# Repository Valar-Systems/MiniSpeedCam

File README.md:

# MiniSpeedCam

## Intro
The MiniSpeedCam tracks vehicle speeds, takes a photo, and uploads the photo and speed data to a server. Use it to track vehicle speeds on your driveway or street.

**Please sign up to the waitlist at [minispeedcam.com](https://minispeedcam.com/) if you're interested in purchasing one. We have not began manufacturing these yet.**

<div style="text-align: center;">

</div>

The firmware is designed to work with [minispeedcam.com](https://minispeedcam.com/) and requires **absolutely no coding or flashing.** The device works right out of the box.

The device creates a WiFi access point when started for the first time. Connect to it with your phone or laptop and enter your WiFi credentials. It will automatically connect to the internet.

All photos and speed data is sent to your account on [minispeedcam.com](https://minispeedcam.com/) where the data can be viewed and downloaded.

If you prefer to use your own server, just modify the Arduino code to point to wherever you'd like. It's completely open-source.

## Special thanks

This device wouldn't be possible without the help of [Mathieu (aka Limpkin)](https://www.limpkin.fr/index.php?post/2022/03/31/CDM324-Doppler-Motion-Sensor-Backpack%2C-now-with-FFTs%21). Thank you for your CDM324 Backpack and your generous help in getting MiniSpeedCam made.

## Accuracy and distance

A 100Hz frequency from the CDM324 corresponds to 2.3km/h speed. By using a tuning fork, we can trick the radar sensor into picking up a specific speed. Using a tuning fork with a frequency of 2048 Hz should trigger a speed reading of 47.1 kph or 29.3 mph ((2048/100) x 2.3)

[Here's a short video](https://youtu.be/ftSh7Fsy7hw) of the tuning fork in action.

Max distance is about 100ft or 30m

## How it works

The device uses the CDM324 which output a very small voltage, depending on how fast the vehicle is traveling. This voltage is amplified by the aplification circuit and sent to the STM32 for processing. The STM32 uses FFT to determine the speed of the vehicle.

The ESP32 handles the speed data, camera, and WiFi. It is connected to the STM32 via UART and polls it for speed data. Once the speed crosses a threshold that you set, the ESP32 takes a photo and sends a POST API call to a server with the data and image encoded in base64. The vehicles maximum speed, image, and date/time are then saved to a server.

## Battery operation

The device consumes about 1.10W while in full operation, and about 0.55W while in sleep mode. The radar sensor is always on, thus consuming 0.55W at all time. When movement is detected, the ESP32 wakes up from light sleep mode, turns on the camera, connects to wifi, takes a photo, sends the data, and goes back to sleep. The process takes about 10 seconds from start to finish. Battery life will depend on how many vehicles the sensor picks up, thus determing how often the ESP32 wakes up. The more vehicles on the road, the larger the battery drain will be.

## Power source

MiniSpeedCam runs on 5V. There are two USB-C ports and a screw terminal that can be used to supply 5V power. The easiest way to power this device is to use an external battery pack with a USB-C cable and plug it into either USB-C plug.

## Reflashing the device

Flashing the firmware is very simple. The STM32 is programmed in STM32 Cube IDE and the ESP32 is programmed in Arduino IDE.  

#### STM32 flashing

First plug your USB cable into the STM32 USB port. Then use the stm32loader python module directly :

```
pip install stm32loader
```

... then with the USB connected to the device (as it uses RTS/CTS signals to control the MCU nRESET and BOOT0 pins):

```
stm32loader -b 115200 -p com_port -e -w -v -s -f F3 MiniSpeedCam.bin
```

If uploading fails, you may use the STM32 Flash loader after performing the following toggling sequence:

1. Press the R0 button
2. Press the B0 button
3. Release R0
4. Release B0

#### ESP32 flashing

Open the Arduino sketch in ArduinoIDE. Be sure you have the libraries at the top of the sketch installed. And be sure your upload options are set up according to the image file in the ESP32_firmware folder.

Optional: ArduinoOTA is also included, allowing you to remotely flash the device from the ArduinoIDE. One caveat is the ESP32 goes to sleep after 10 minutes of being powered on. Just cycle the power to it and you'll have 10 minutes to upload your sketch.

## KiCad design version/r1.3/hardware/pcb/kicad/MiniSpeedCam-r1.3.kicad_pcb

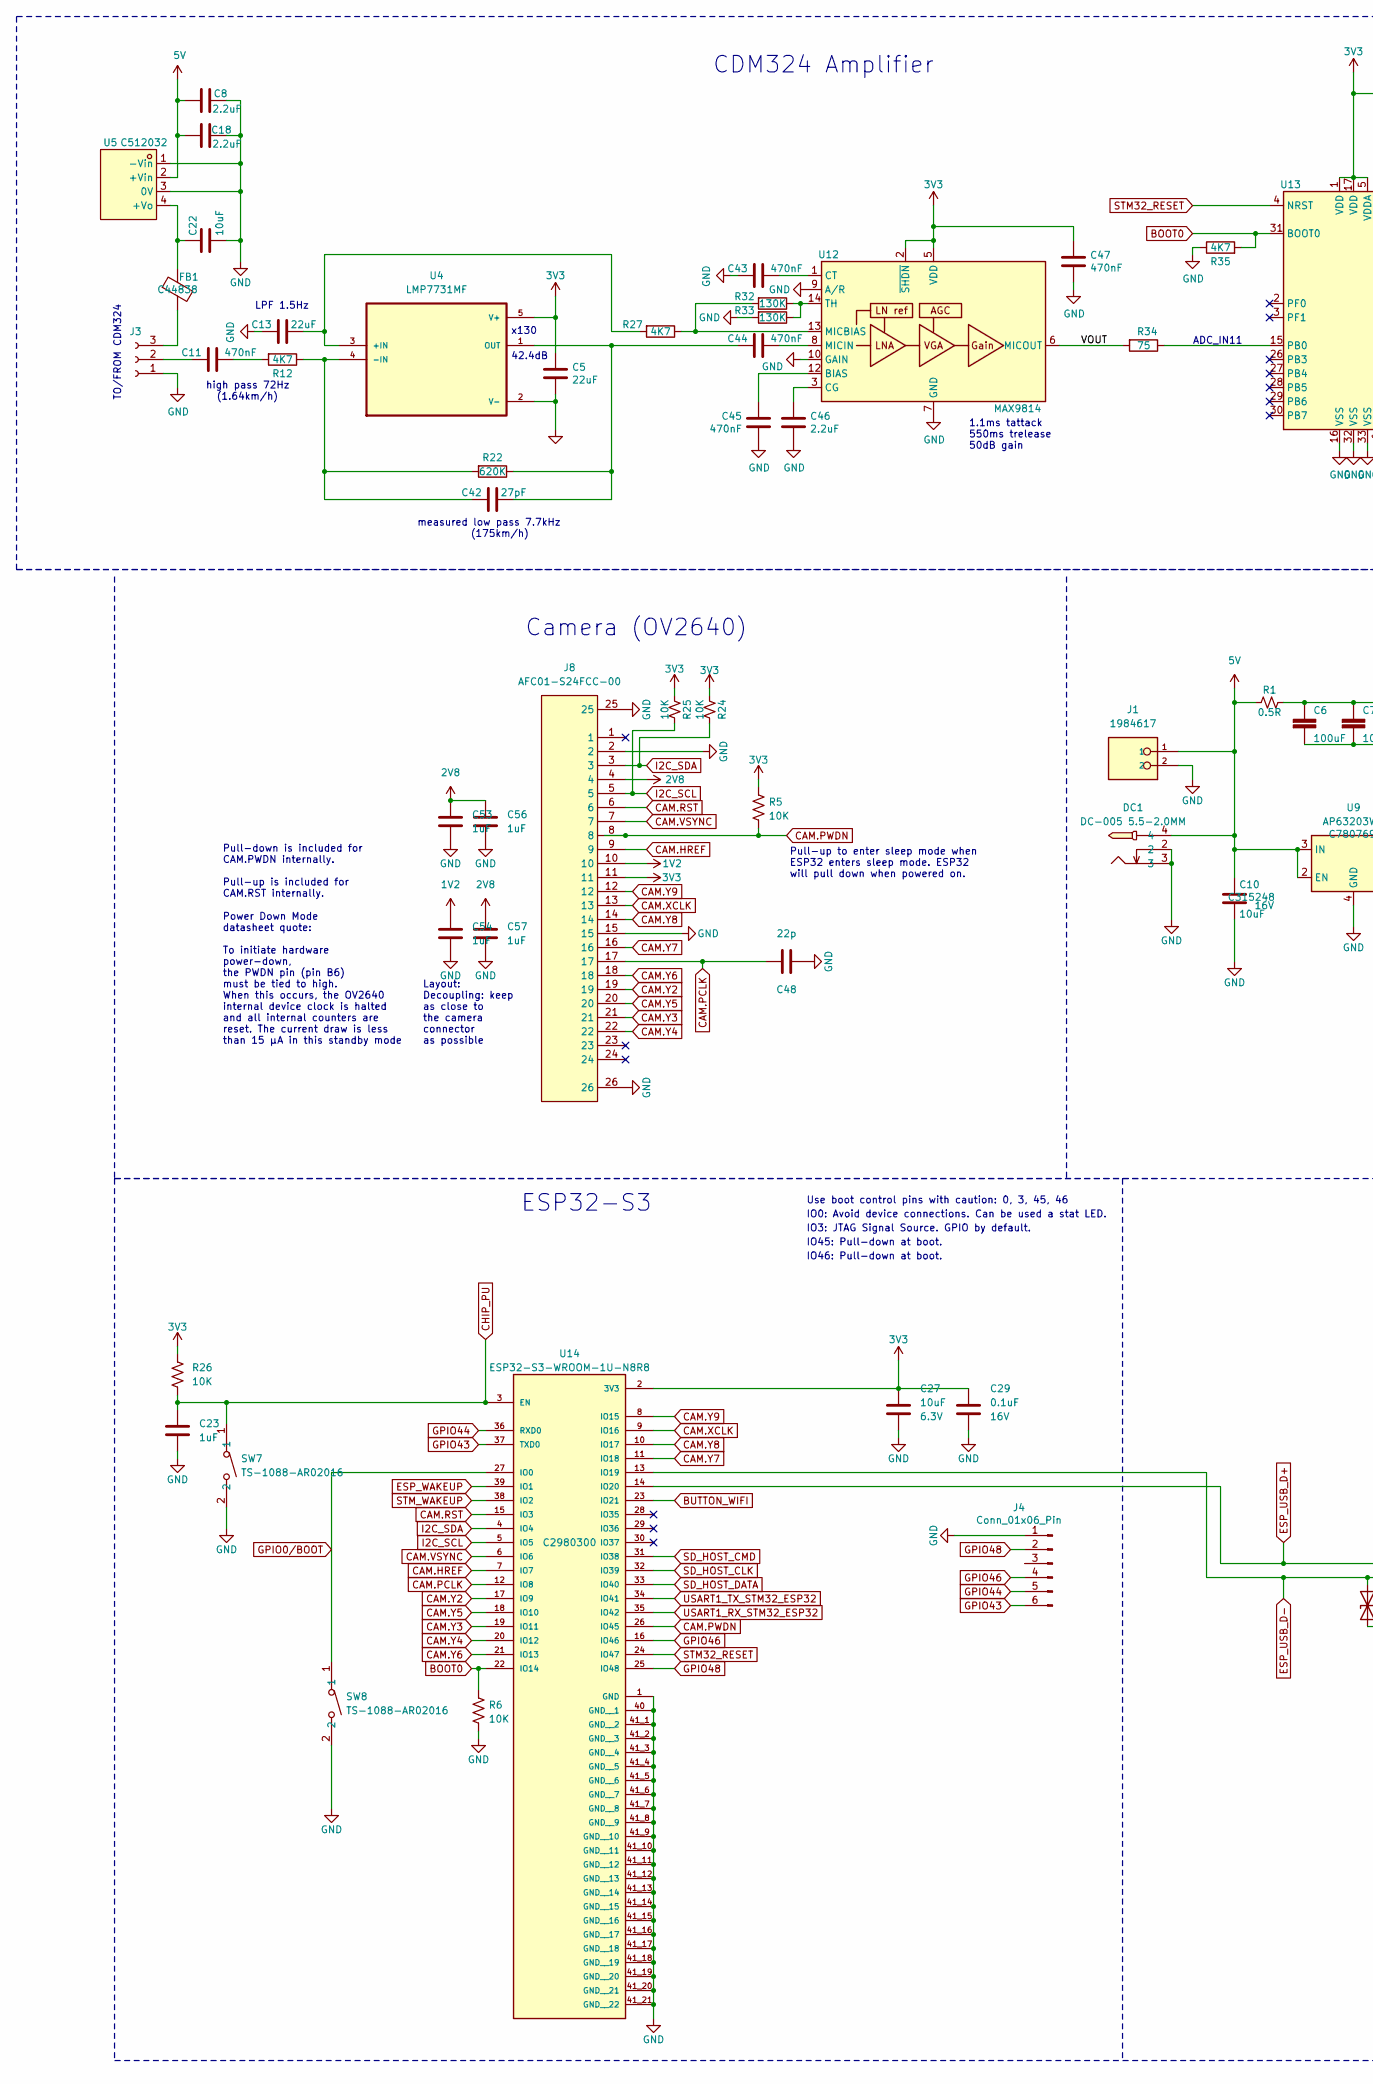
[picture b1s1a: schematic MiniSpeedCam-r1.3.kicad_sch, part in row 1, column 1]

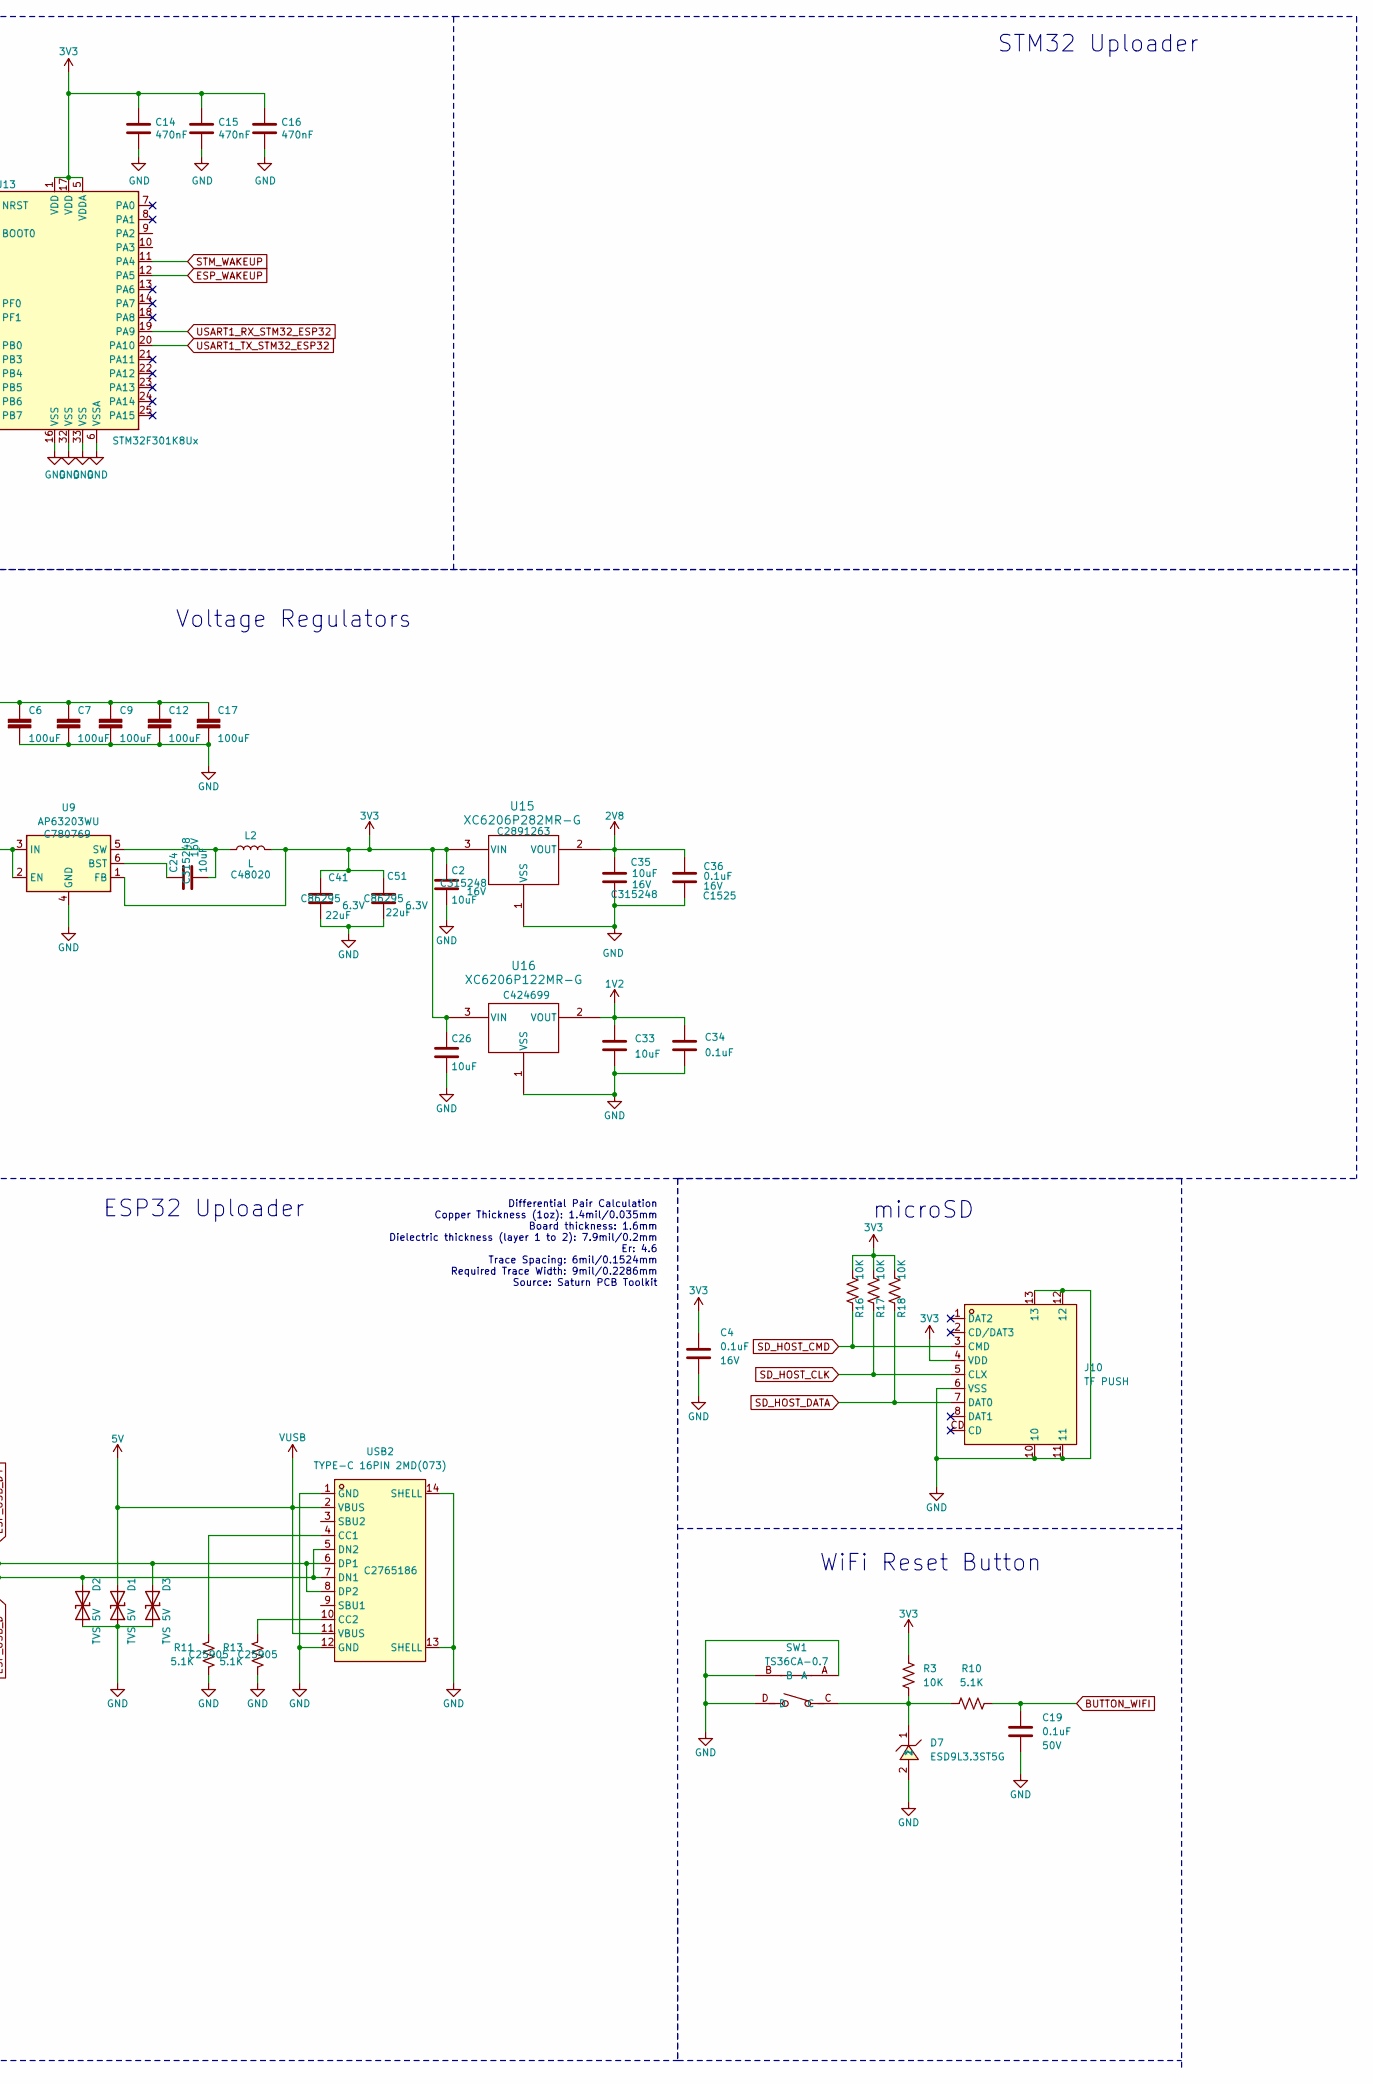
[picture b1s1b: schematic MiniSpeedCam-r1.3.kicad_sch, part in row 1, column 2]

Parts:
C2, C10, C22, C24, C26, C33, C35: 10uF; C_0402_1005Metric; Voltage 16V; Tolerance 10%; LCSC C315248
C4, C29, C34, C36: 0.1uF; C_0402_1005Metric; Voltage 16V; Tolerance 10%; LCSC C1525
C5, C13: 22uF; C_0603_1608Metric; LCSC C86295
C6, C7, C9, C12, C17: 100uF; C_1206_3216Metric; Voltage ???; LCSC C7432784
C8, C18, C46: 2.2uF; C_0603_1608Metric; LCSC C1607
C11, C14, C15, C16, C43, C44, C45, C47: 470nF; C_0402_1005Metric; LCSC C47339
C19: 0.1uF; C_0402_1005Metric; Voltage 50V; Tolerance 10%; LCSC C1525
C23, C53: 10u_0402_CL05A105KA5NQNC; C_0402_1005Metric; Rating 25V; Tolerance 10%; MPN CL05A105KA5NQNC; LCSC C52923
C27: 10uF; C_0402_1005Metric; Voltage 6.3V; Tolerance 20%; LCSC C315248
C41, C51: 22uF; C_0603_1608Metric; Voltage 6.3V; Tolerance 20%; LCSC C86295
C42: 27pF; C_0603_1608Metric; LCSC C1656
C48: 22p_0402_0402CG220J500NT; C_0402_1005Metric; Rating 50V; Tolerance 5%; MPN 0402CG220J500NT; LCSC C1555
C54, C56, C57: 10u_0402_CL05A105KA5NQNC; C_0402_1005Metric; Tolerance 10%; Rating 25V; MPN CL05A105KA5NQNC; LCSC C52923
D1, D2, D3: SOD-523_BSD5C051L; D_SOD-523; MPN BSD5C051L; LCSC C151983
D7: ESD9L3.3ST5G; SOD-923_L0.8-W0.6-LS1.0-RD; LCSC C233387
DC1: DC-005 5.5-2.0MM; DC-IN-TH_DC-005-5.5-2.0; LCSC C16214
FB1: Ferrite_Bead; L_0805_2012Metric; LCSC C44838
J1: 1984617; PHOENIX_1984617; PARTREV 22.08.2018; LCSC C466970
J3: Conn_01x03_Female; PinHeader_1x03_P2.54mm_Vertical
J4: Conn_01x06_Pin; PinHeader_1x06_P2.54mm_Vertical
J8: AFC01-S24FCC-00; FPC-SMD_P0.5-24P_FGS-XJ-H2.0; LCSC C262276
J10: TF PUSH; TF-SMD_TF-PUSH; LCSC C393941
L2: L; IND-SMD_L3.0-W3.0_FNR30XXS; LCSC C48020
R1: 0.5R; R_0603_1608Metric; LCSC C2934253
R3, R5, R6, R16, R17, R18, R24, R25, R26: 10K; R_0402_1005Metric; LCSC C25744
R10, R11, R13: 5.1K; R_0402_1005Metric; LCSC C25905
R12, R27, R35: 4K7; R_0603_1608Metric; LCSC C99782
R22: 620K; R_0603_1608Metric; LCSC C68737
R32, R33: 130K; R_0603_1608Metric; LCSC C22795
R34: 75; R_0402_1005Metric; LCSC C137841
SW1: TS36CA-0.7; SW-SMD_TS36CA; LCSC C412365
SW7, SW8: TS-1088-AR02016; SW-SMD_L3.9-W3.0-P4.45; LCSC C720477
U4: LMP7731MF; SOT-23-5_L3.0-W1.7-P0.95-LS2.8-BL; LCSC C202252
U5: B0505S-1W_C512032; PWRM-TH_BXXXXS-1W; LCSC C512032
U9: AP63203WU; TSOT-23-6; LCSC C780769
U12: MAX9814; DFN-14-1EP_3x3mm_P0.4mm_EP1.78x2.35mm; LCSC C41714
U13: STM32F301K8Ux; QFN-32-1EP_5x5mm_P0.5mm_EP3.45x3.45mm; LCSC C111684
U14: ESP32-S3-WROOM-1U-N8R8; XCVR_ESP32-S3-WROOM-1U-N8R8; PARTREV v1.1; LCSC C2980300
U15: XC6206P282MR-G; SOT-23_TOR; LCSC C2891263
U16: XC6206P122MR-G; SOT-23_TOR; LCSC C424699
USB2: TYPE-C 16PIN 2MD(073); USB-C-SMD_TYPE-C-6PIN-2MD-073; LCSC C2765186

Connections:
1V2: C33.1, C34.1, C54.2, J8.10, U16.2 (VOUT)
2V8: C35.1, C36.1, C53.1, C56.2, C57.2, J8.4, U15.2 (VOUT)
3V3: C2.1, C4.1, C5.1, C14.1, C15.1, C16.1, C26.1, C27.1, C29.1, C41.2, C47.1, C51.2, J8.11, J10.4 (VDD), L2.2, R3.1, R5.1, R16.1, R17.1, R18.1, R24.1, R25.1, R26.1, U4.5 (V+), U9.1 (FB), U12.2 (~SHDN), U12.5 (VDD), U13.1 (VDD), U13.5 (VDDA), U13.17 (VDD), U14.2 (3V3), U15.3 (VIN), U16.3 (VIN)
5V: C8.1, C10.1, C18.1, D1.2 (A2), DC1.4, J1.1, R1.1, U5.2 (+Vin), U9.2 (EN), U9.3 (IN), USB2.2 (VBUS), USB2.11 (VBUS)
/VOUT: R34.2, U12.6 (MICOUT)
BOOT0: R6.1, R35.2, U13.31 (BOOT0), U14.22 (IO14)
BUTTON_WIFI: C19.2, R10.2, U14.23 (IO21)
CAM.HREF: J8.9, U14.7 (IO7)
CAM.PCLK: C48.1, J8.17, U14.12 (IO8)
CAM.PWDN: J8.8, R5.2, U14.26 (IO45)
CAM.RST: J8.6, U14.15 (IO3)
CAM.VSYNC: J8.7, U14.6 (IO6)
CAM.XCLK: J8.13, U14.9 (IO16)
CAM.Y2: J8.19, U14.17 (IO9)
CAM.Y3: J8.21, U14.19 (IO11)
CAM.Y4: J8.22, U14.20 (IO12)
CAM.Y5: J8.20, U14.18 (IO10)
CAM.Y6: J8.18, U14.21 (IO13)
CAM.Y7: J8.16, U14.11 (IO18)
CAM.Y8: J8.14, U14.10 (IO17)
CAM.Y9: J8.12, U14.8 (IO15)
CHIP_PU: C23.1, R26.2, SW7.1, U14.3 (EN)
ESP_USB_D+: D3.2 (A2), U14.14 (IO20), USB2.6 (DP1), USB2.8 (DP2)
ESP_USB_D-: D2.2 (A2), U14.13 (IO19), USB2.5 (DN2), USB2.7 (DN1)
ESP_WAKEUP: U13.12 (PA5), U14.39 (IO1)
GND: C2.2, C4.2, C5.2, C6.2, C7.2, C8.2, C9.2, C10.2, C12.2, C13.2, C14.2, C15.2, C16.2, C17.2, C18.2, C19.1, C22.2, C23.2, C26.2, C27.2, C29.2, C33.2, C34.2, C35.2, C36.2, C41.1, C43.2, C45.2, C46.2, C47.2, C48.2, C51.1, C53.2, C54.1, C56.1, C57.1, D1.1 (A1), D2.1 (A1), D3.1 (A1), D7.2, DC1.2, DC1.3, J1.2, J3.1, J4.1, J8.2, J8.15, J8.25, J8.26, J10.6 (VSS), J10.10, J10.11, J10.12, J10.13, R6.2, R11.2, R13.1, R33.2, R35.1, SW1.A, SW1.B, SW1.D, SW7.2, SW8.2, U4.2 (V-), U5.1 (-Vin), U5.3 (0V), U9.4 (GND), U12.4 (GND), U12.7 (GND), U12.9 (A/R), U12.10 (GAIN), U12.11 (GND), U12.15 (GND), U13.6 (VSSA), U13.16 (VSS), U13.32 (VSS), U13.33 (VSS), U14.1 (GND), U14.40 (GND__1), U14.41_1 (GND__2), U14.41_2 (GND__3), U14.41_3 (GND__4), U14.41_4 (GND__5), U14.41_5 (GND__6), U14.41_6 (GND__7), U14.41_7 (GND__8), U14.41_8 (GND__9), U14.41_9 (GND__10), U14.41_10 (GND__11), U14.41_11 (GND__12), U14.41_12 (GND__13), U14.41_13 (GND__14), U14.41_14 (GND__15), U14.41_15 (GND__16), U14.41_16 (GND__17), U14.41_17 (GND__18), U14.41_18 (GND__19), U14.41_19 (GND__20), U14.41_20 (GND__21), U14.41_21 (GND__22), U15.1 (VSS), U16.1 (VSS), USB2.1 (GND), USB2.12 (GND), USB2.13 (SHELL), USB2.14 (SHELL)
GPIO0/BOOT: SW8.1, U14.27 (IO0)
GPIO43: J4.6, U14.37 (TXD0)
GPIO44: J4.5, U14.36 (RXD0)
GPIO46: J4.4, U14.16 (IO46)
GPIO48: J4.2, U14.25 (IO48)
I2C_SCL: J8.5, R25.2, U14.5 (IO5)
I2C_SDA: J8.3, R24.2, U14.4 (IO4)
unnamed: C11.1, R12.2
unnamed: C6.1, C7.1, C9.1, C12.1, C17.1, R1.2
unnamed: D7.1, R3.2, R10.1, SW1.C
unnamed: C11.2, J3.2
unnamed: FB1.2, J3.3
unnamed: C13.1, R27.2, U4.3 (+IN)
unnamed: C42.2, R12.1, R22.2, U4.4 (-IN)
unnamed: C42.1, C44.2, R22.1, U4.1 (OUT)
unnamed: C22.1, FB1.1, U5.4 (+Vo)
unnamed: C24.1, U9.6 (BST)
unnamed: C24.2, L2.1, U9.5 (SW)
unnamed: C45.1, U12.12 (BIAS)
unnamed: C46.1, U12.3 (CG)
unnamed: C43.1, U12.1 (CT)
unnamed: R27.1, R32.2, U12.13 (MICBIAS)
unnamed: C44.1, U12.8 (MICIN)
unnamed: R32.1, R33.1, U12.14 (TH)
unnamed: R34.1, U13.15 (PB0)
unnamed: R11.1, USB2.4 (CC1)
unnamed: R13.2, USB2.10 (CC2)
SD_HOST_CLK: J10.5 (CLX), R17.2, U14.32 (IO39)
SD_HOST_CMD: J10.3 (CMD), R16.2, U14.31 (IO38)
SD_HOST_DATA: J10.7 (DAT0), R18.2, U14.33 (IO40)
STM32_RESET: U13.4 (NRST), U14.24 (IO47)
STM_WAKEUP: U13.11 (PA4), U14.38 (IO2)
USART1_RX_STM32_ESP32: U13.19 (PA9), U14.35 (IO42)
USART1_TX_STM32_ESP32: U13.20 (PA10), U14.34 (IO41)

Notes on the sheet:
1.1ms tattack 550ms trelease 50dB gain
ADC_IN11
Differential Pair Calculation Copper Thickness (1oz): 1.4mil/0.035mm Board thickness: 1.6mm Dielectric thickness (layer 1 to 2): 7.9mil/0.2mm Er: 4.6 Trace Spacing: 6mil/0.1524mm Required Trace Width: 9mil/0.2286mm Source: Saturn PCB Toolkit
IO0: Avoid device connections. Can be used a stat LED.
WiFi Reset Button
Voltage Regulators
high pass 72Hz (1.64km/h)
TO/FROM CDM324
Pull-down is included for CAM.PWDN internally. Pull-up is included for CAM.RST internally.
IO46: Pull-down at boot.
ESP32-S3
Power Down Mode datasheet quote: To initiate hardware power-down, the PWDN pin (pin B6) must be tied to high. When this occurs, the OV2640 internal device clock is halted and all internal counters are reset. The current draw is less than 15 µA in this standby mode
42.4dB
x130
ESP32 Uploader
Pull-up to enter sleep mode when ESP32 enters sleep mode. ESP32 will pull down when powered on.
Use boot control pins with caution: 0, 3, 45, 46
CDM324 Amplifier
microSD
IO45: Pull-down at boot.
Camera (OV2640)
Layout: Decoupling: keep as close to the camera connector as possible
measured low pass 7.7kHz (175km/h)
LPF 1.5Hz
IO3: JTAG Signal Source. GPIO by default.
STM32 Uploader

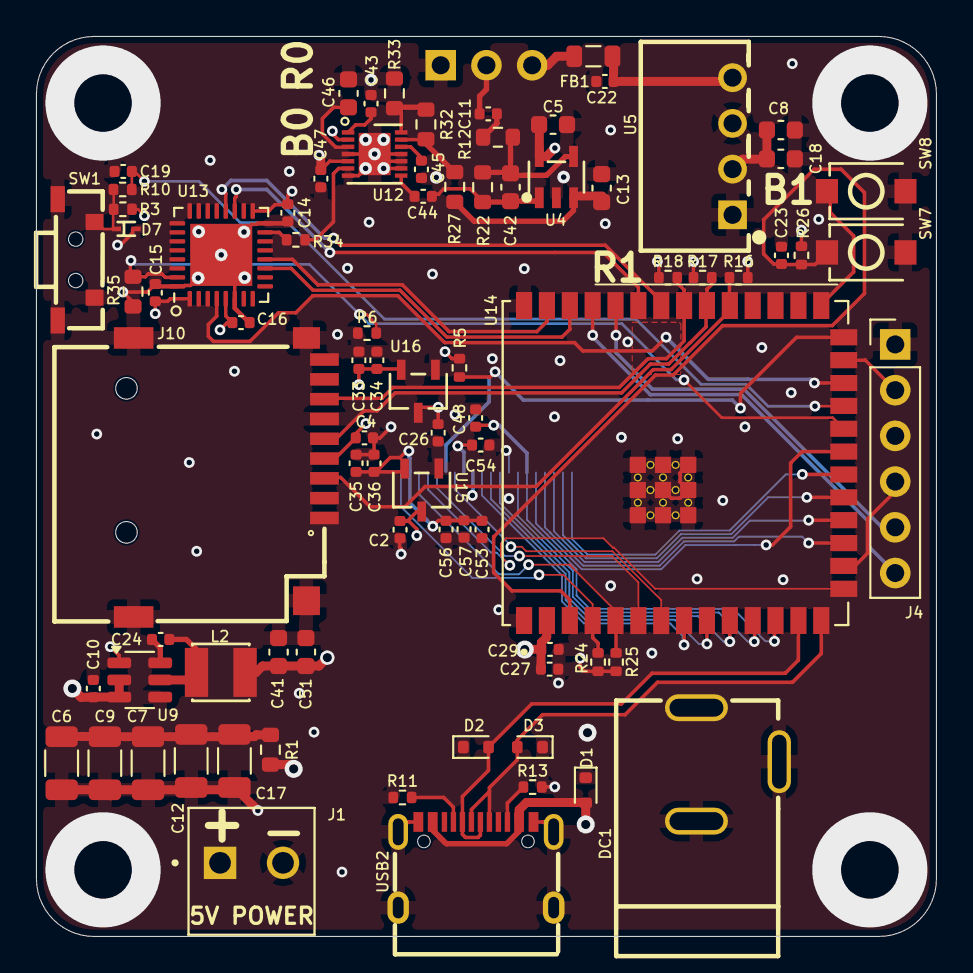
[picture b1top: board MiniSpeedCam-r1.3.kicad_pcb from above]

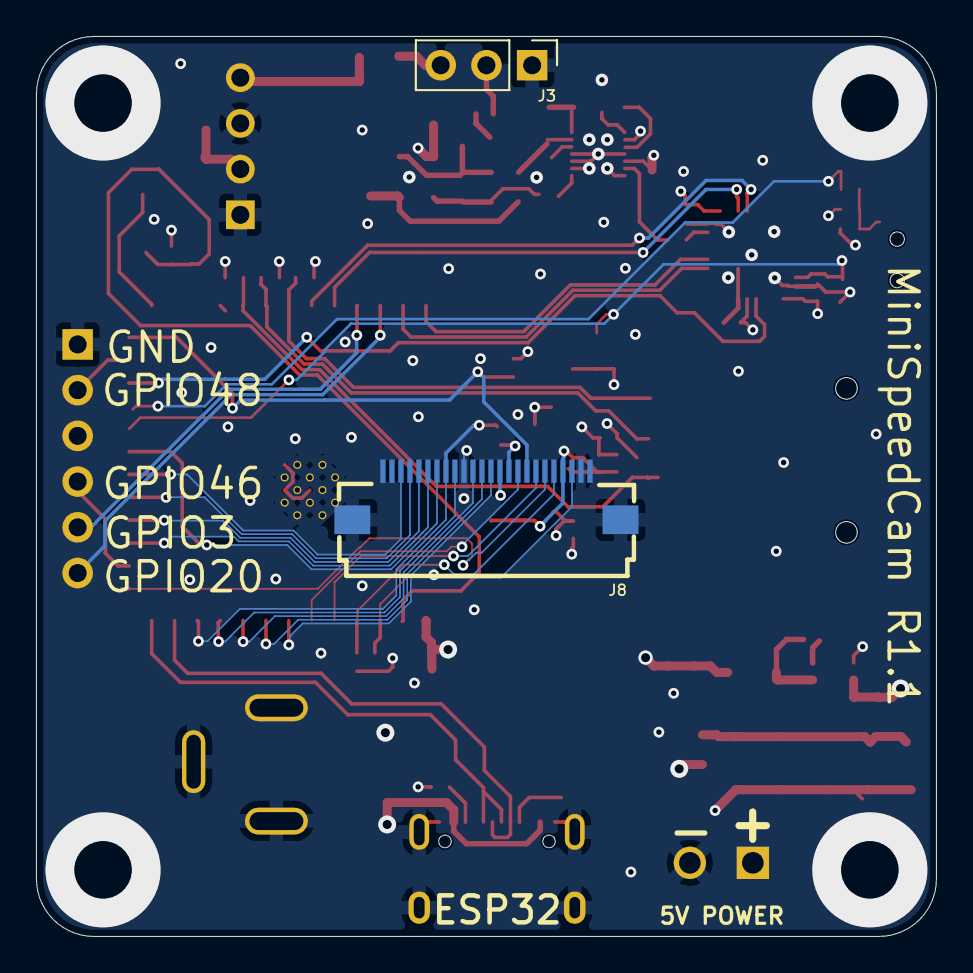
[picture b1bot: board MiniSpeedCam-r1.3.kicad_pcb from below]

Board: 4 copper layers, 50.0 x 50.0 mm, 84 parts (2 on the bottom side), 60 nets.

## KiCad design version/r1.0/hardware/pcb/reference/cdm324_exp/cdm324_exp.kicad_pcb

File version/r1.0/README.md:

# MiniSpeedCam R1.0

#### STM32 flashing

R1.0 has a problem with the automatic download circuit on the STM32.

The STM32 **MUST** be entered into Boot mode manually using the B0 and R0 button.

First plug your USB cable into the STM32 USB port. Then use the stm32loader python module directly :

```
pip install stm32loader
```

... then with the USB connected to the device.

In the terminal, navigate to the folder that houses the binary, in the Release folder and run the following command. Replace the "com_port" with the correct COM port.

```
stm32loader -b 115200 -p com_port -e -w -v -s -f F3 MiniSpeedCam.bin
```

1. Press the R0 button
2. Press the B0 button
3. Release R0
4. Release B0

#### ESP32 flashing

Open the Arduino sketch in ArduinoIDE. Be sure you have the libraries at the top of the sketch installed. And be sure your upload options are set up according to the image file in the ESP32_firmware folder.

Optional: ArduinoOTA is also included, allowing you to remotely flash the device from the ArduinoIDE. One caveat is the ESP32 goes to sleep after 10 minutes of being powered on. Just cycle the power to it and you'll have 10 minutes to upload your sketch.

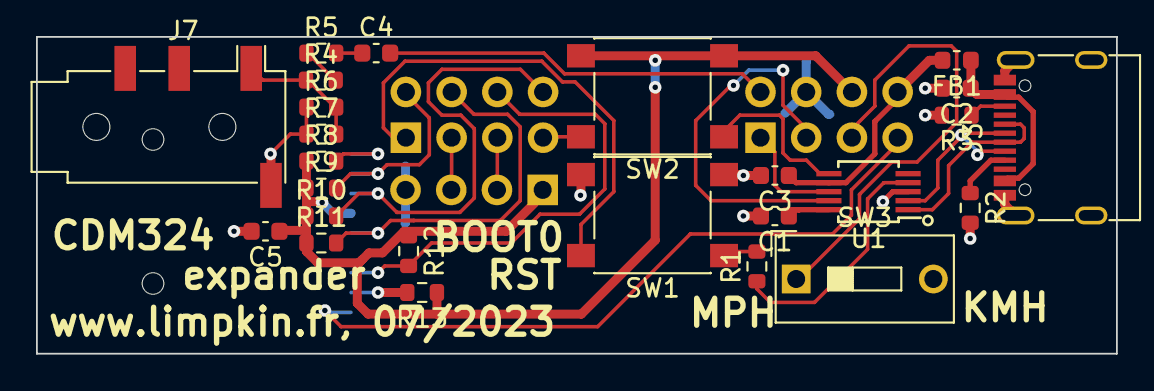
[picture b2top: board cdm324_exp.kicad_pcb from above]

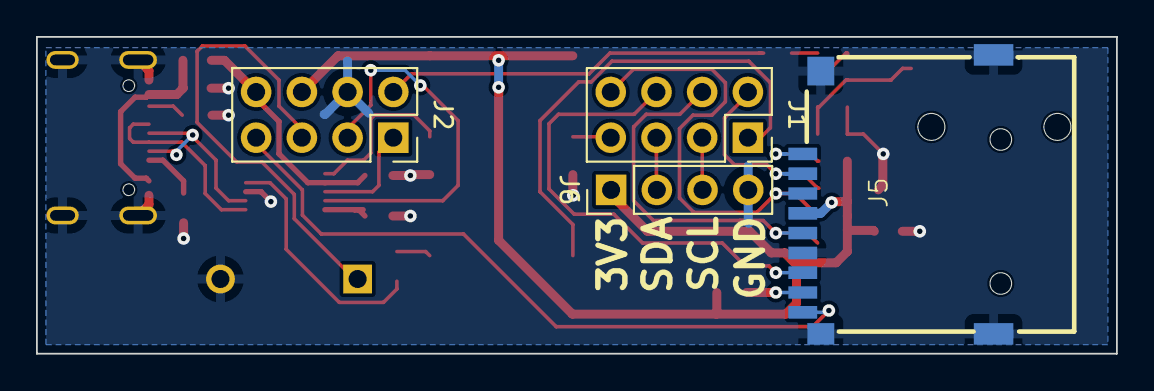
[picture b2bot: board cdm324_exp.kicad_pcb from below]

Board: 2 copper layers, 60.0 x 17.6 mm, 29 parts (4 on the bottom side), 28 nets.

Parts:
C1, C2, C3, C4, C5: 1uF; C_0603_1608Metric
FB1: FerriteBead; L_0603_1608Metric
J1, J2: Conn_02x04_Odd_Even; PinSocket_2x04_P2.54mm_Vertical
J3: USB_C_Receptacle_USB2.0; USB_C_Receptacle_G-Switch_GT-USB-7010ASV
J5: Micro_SD_Card_Det1; XKTF-015-N
J6: Conn_01x04_Socket; PinHeader_1x04_P2.54mm_Vertical
J7: AudioJack4; Jack_3.5mm_PJ320D_Horizontal
R1, R4, R5, R6, R7: 1k; R_0603_1608Metric
R2, R3: 5.1k; R_0603_1608Metric
R8, R9, R10, R11, R12, R13: 49k9; R_0603_1608Metric
SW1, SW2: SW_Push; SW_Push_1P1T_NO_6x6mm_H9.5mm
SW3: SW_DIP_x01; SW_DIP_SPSTx01_Slide_9.78x4.72mm_W7.62mm_P2.54mm
U1: CH340X; MSOP-10_3x3mm_P0.5mm

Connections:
+3V3: C5.1, J2.6, J5.4 (VDD), J6.1, R8.1, R9.1, R10.1, R11.1, R12.1, R13.1, SW2.2
/BOOT0: J1.7, SW2.1, U1.6 (TNOW)
/I2C_SCL: J1.3, J6.3
/I2C_SDA: J1.5, J6.2
/PA0: J2.7, J5.9 (DET)
/PA1: J2.5, SW3.1
/SPI_MISO: J1.6, J5.7 (DAT0), R12.2
/SPI_MOSI: J1.8, J5.3 (CMD), R10.2
/SPI_SCK: J1.4, J5.5 (CLK), R11.2
/SPI_nCS: J1.2, J5.2 (DAT3/CD), R9.2
/UART_RX: J2.1, U1.8 (TXD)
/UART_TX: J2.3, U1.9 (RXD)
/VOUT: C4.2, J2.2
/nRESET: J1.1, R1.2, SW1.1
GND: C1.2, C2.2, C3.2, C5.2, J2.4, J3.A1 (GND), J3.A12 (GND), J3.B1 (GND), J3.B12 (GND), J3.S1 (SHIELD), J5.6 (VSS), J5.10 (SHIELD), J6.4, J7.S, R2.2, R3.2, R6.1, R7.1, SW1.2, SW3.2, U1.3 (GND)
unnamed: C2.1, FB1.1, J3.A4 (VBUS), J3.A9 (VBUS), J3.B4 (VBUS), J3.B9 (VBUS)
unnamed: C4.1, R5.2
unnamed: J3.A5 (CC1), R2.1
unnamed: J3.B5 (CC2), R3.1
unnamed: J5.8 (DAT1), R13.2
unnamed: J5.1 (DAT2), R8.2
unnamed: J7.T, R4.1, R6.2, R7.2
unnamed: R4.2, R5.1
unnamed: J3.A6 (D+), J3.B6 (D+), U1.1 (UD+)
unnamed: J3.A7 (D-), J3.B7 (D-), U1.2 (UD-)
unnamed: C1.1, U1.10 (V3)
unnamed: R1.1, U1.4 (~RTS)
VCC: C3.1, FB1.2, J2.8, U1.7 (VCC)

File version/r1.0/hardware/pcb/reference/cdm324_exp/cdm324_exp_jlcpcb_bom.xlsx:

Designator | Comment | Footprint | JLCPCB Part #
C1, C2, C3, C4, C5 | 1uF | Capacitor_SMD:C_0603_1608Metric | C1592
FB1 | FerriteBead | Inductor_SMD:L_0603_1608Metric | C14709
J1, J2 | Conn_02x04_Odd_Even | Connector_PinSocket_2.54mm:PinSocket_2x04_P2.54mm_Vertical | C2685133
J3 | USB_C_Receptacle_USB2.0 | Connector_USB:USB_C_Receptacle_G-Switch_GT-USB-7010ASV | C2988369
J5 | Micro_SD_Card_Det1 | lib:XKTF-015-N | C381082
J7 | AudioJack4 | Connector_Audio:Jack_3.5mm_PJ320D_Horizontal | C431535
R1, R4, R5, R6, R7 | 1k | Resistor_SMD:R_0603_1608Metric | C22548
R2, R3 | 5.1k | Resistor_SMD:R_0603_1608Metric | C105580
R8, R9, R10, R11, R12, R13 | 49k9 | Resistor_SMD:R_0603_1608Metric | C114624
SW1, SW2 | SW_Push | Button_Switch_SMD:SW_Push_1P1T_NO_6x6mm_H9.5mm | C255812
SW3 | SW_DIP_x01 | Button_Switch_THT:SW_DIP_SPSTx01_Slide_9.78x4.72mm_W7.62mm_P2.54mm | C126888
U1 | CH340X | Package_SO:MSOP-10_3x3mm_P0.5mm | C3035748

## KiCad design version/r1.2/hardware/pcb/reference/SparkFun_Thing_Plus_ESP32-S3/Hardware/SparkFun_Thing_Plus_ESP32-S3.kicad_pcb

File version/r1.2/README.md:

# MiniSpeedCam R1.2

Hardware version R1.2

ESP32 Upload Settings. **Menu -> Tools**

- USB CDC On Boot: Enabled
- CPU Frequency: 240MHz (WiFi)
- Core Debug Level: Verbose
- Events Run On: Core 1
- Flash Size: 8MB 
- Arduino Runs On: Core 1
- Partition Scheme: 8MB with spiffs
- PSRAM: OPI PSRAM

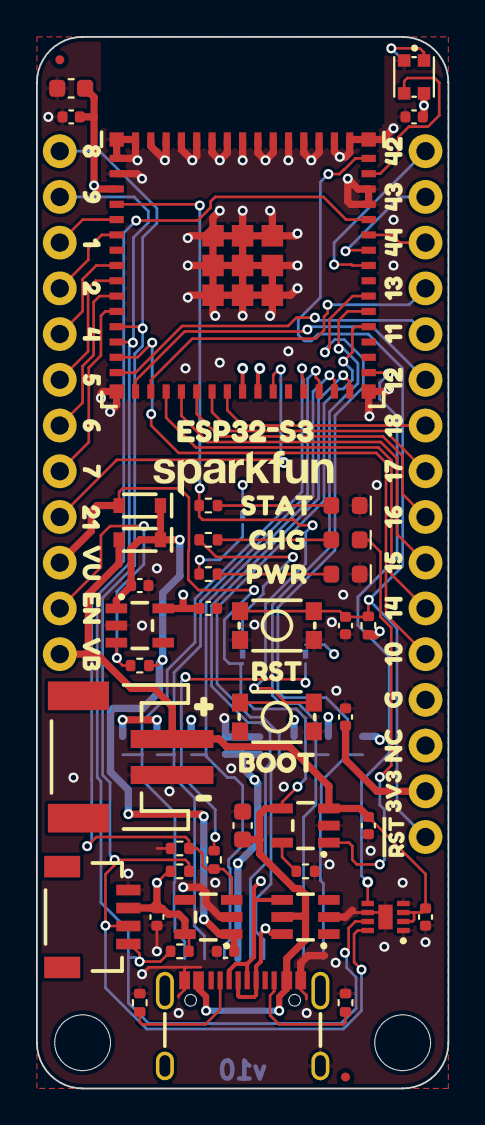
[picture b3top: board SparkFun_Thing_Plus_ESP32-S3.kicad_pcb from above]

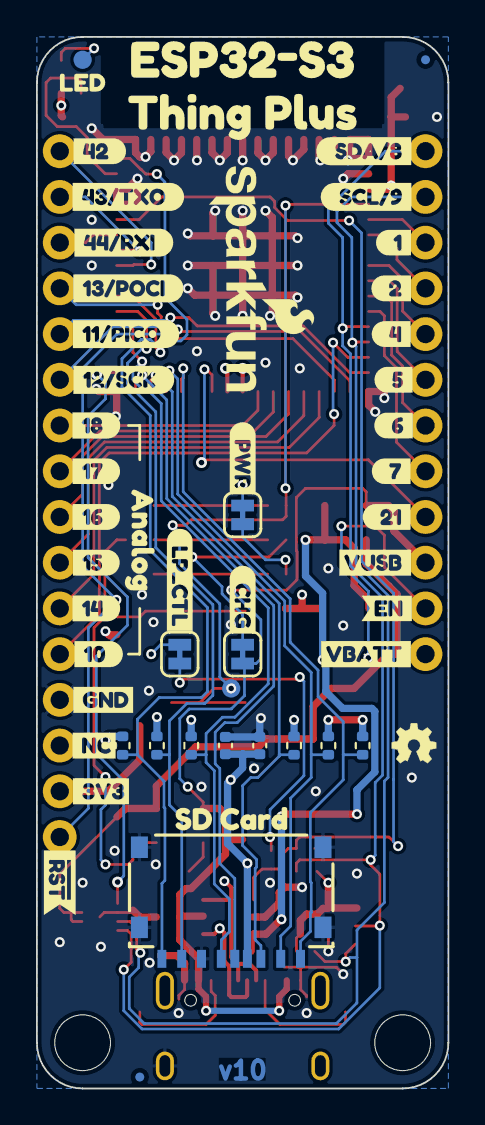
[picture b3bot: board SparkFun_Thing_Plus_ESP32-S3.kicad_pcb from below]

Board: 4 copper layers, 22.9 x 58.4 mm, 137 parts (53 on the bottom side), 53 nets.

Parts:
C1: 22uF; C_0603_1608Metric
C2, C5, C8, C11: 0.1uF; C_0402_1005Metric
C3, C4: 10uF; C_0402_1005Metric
C6, C13: 1.0uF; C_0402_1005Metric
C7, C12: 4.7uF; C_0402_1005Metric
C9: 4.7uF; C_0603_1608Metric
C10, C14: 2.2uF; C_0402_1005Metric
D1: Green; LED_0603_1608Metric_Green
D2, D3: BAT60A; SOD-323
D4: Yellow; LED_0603_1608Metric_Yellow
D5: Red; LED_0603_1608Metric_Red
D6: WS2812B; WS2812_2020
FID1, FID2, FID3, FID4: Fiducial_0.5mm; Fiducial_0.5mm_Mask1mm
G3: OSHW_Logo; Creative_Commons_License
J1: USB_C_Receptacle; USB-C_16
J2: microSD_Friction; microSD_Friction_Fit_Common
J3: JST_2mm_LiPo; JST_SMD_2.0mm-2
J4: Qwiic_RA; JST_SMD_1.0mm-4_RA
JP1, JP2, JP3: Jumper_2_NC_Trace
R1, R2, R3, R4, R5, R6, R8, R17: 10k; R_0402_1005Metric
R7: 330; R_0402_1005Metric
R9: 4.7k; R_0402_1005Metric
R10, R11: 5.1k; R_0402_1005Metric
R12, R15: 2.2k; R_0402_1005Metric
R13, R19: 100k; R_0402_1005Metric
R14: 1k; R_0402_1005Metric
R16: 2.0k; R_0402_1005Metric
Ref**: Val**; OSHW_Logo_2.5mm
ST1, ST3: Standoff
SW1, SW2: SMD_4.6x2.8mm_h2.5mm; Push_SMD_4.6x2.8mm_h2.5mm
TP1, TP2: 1.0mm; TestPoint-1.0mm
U1, U6: RT9080-3.3; SOT23-5
U2: DT1042-04SO; SOT23-6
U3: ESP32-S3-MINI; ESP32-MINI
U4: MAX17048; DFN-8
U5: MCP73831; SOT23-5
U9: Ordering_Instructions
U10: ThingPlus
kibuzzard-65A99A9C: G***; kibuzzard-65A99A9C
kibuzzard-65A99AA3: G***; kibuzzard-65A99AA3
kibuzzard-65A99E72: G***; kibuzzard-65A99E72
kibuzzard-65A403E0: G***; kibuzzard-65A403E0
kibuzzard-65A992E3: G***; kibuzzard-65A992E3
kibuzzard-65A9923A: G***; kibuzzard-65A9923A
kibuzzard-65A9926C: G***; kibuzzard-65A9926C
kibuzzard-65A9926F: G***; kibuzzard-65A9926F
kibuzzard-65A9927C: G***; kibuzzard-65A9927C
kibuzzard-65A9927F: G***; kibuzzard-65A9927F
kibuzzard-65A9928A: G***; kibuzzard-65A9928A
kibuzzard-65A9928E: G***; kibuzzard-65A9928E
kibuzzard-65A9933C: G***; kibuzzard-65A9933C
kibuzzard-65A9934B: G***; kibuzzard-65A9934B
kibuzzard-65A9935C: G***; kibuzzard-65A9935C
kibuzzard-65A9936B: G***; kibuzzard-65A9936B
kibuzzard-65A9990D: G***; kibuzzard-65A9990D
kibuzzard-65A99252: G***; kibuzzard-65A99252
kibuzzard-65A99268: G***; kibuzzard-65A99268
kibuzzard-65A99274: G***; kibuzzard-65A99274
kibuzzard-65A99278: G***; kibuzzard-65A99278
kibuzzard-65A99283: G***; kibuzzard-65A99283
kibuzzard-65A99287: G***; kibuzzard-65A99287
kibuzzard-65A99292: G***; kibuzzard-65A99292
kibuzzard-65A99297: G***; kibuzzard-65A99297
kibuzzard-65A99335: G***; kibuzzard-65A99335
kibuzzard-65A99346: G***; kibuzzard-65A99346
kibuzzard-65A99350: G***; kibuzzard-65A99350
kibuzzard-65A99354: G***; kibuzzard-65A99354
kibuzzard-65A99359: G***; kibuzzard-65A99359
kibuzzard-65A99360: G***; kibuzzard-65A99360
kibuzzard-65A99364: G***; kibuzzard-65A99364
kibuzzard-65A99367: G***; kibuzzard-65A99367
kibuzzard-65A99912: G***; kibuzzard-65A99912
kibuzzard-65A99933: G***; kibuzzard-65A99933
kibuzzard-65AA9C9F: G***; kibuzzard-65AA9C9F
kibuzzard-656A3D93: G***; kibuzzard-656A3D93
kibuzzard-656A31AF: G***; kibuzzard-656A31AF
kibuzzard-656A32A0: G***; kibuzzard-656A32A0
kibuzzard-656A32FE: G***; kibuzzard-656A32FE
kibuzzard-656A35A5: G***; kibuzzard-656A35A5
kibuzzard-656A35AD: G***; kibuzzard-656A35AD
kibuzzard-656A35B5: G***; kibuzzard-656A35B5
kibuzzard-656A35BC: G***; kibuzzard-656A35BC
kibuzzard-656A35C4: G***; kibuzzard-656A35C4
kibuzzard-656A36A2: G***; kibuzzard-656A36A2
kibuzzard-656A36A7: G***; kibuzzard-656A36A7
kibuzzard-656A36C2: G***; kibuzzard-656A36C2
kibuzzard-656A47C5: G***; kibuzzard-656A47C5
kibuzzard-656A359E: G***; kibuzzard-656A359E
kibuzzard-656A361F: G***; kibuzzard-656A361F
kibuzzard-656A367B: G***; kibuzzard-656A367B
kibuzzard-656A368C: G***; kibuzzard-656A368C
kibuzzard-656A482A: G***; kibuzzard-656A482A
kibuzzard-656A3526: G***; kibuzzard-656A3526
kibuzzard-656A3552: G***; kibuzzard-656A3552
kibuzzard-656A3559: G***; kibuzzard-656A3559
kibuzzard-656A3560: G***; kibuzzard-656A3560
kibuzzard-656A3567: G***; kibuzzard-656A3567
kibuzzard-656A3591: G***; kibuzzard-656A3591
kibuzzard-656A3598: G***; kibuzzard-656A3598
kibuzzard-656A3668: G***; kibuzzard-656A3668
kibuzzard-656A3687: G***; kibuzzard-656A3687
kibuzzard-656A3691: G***; kibuzzard-656A3691
kibuzzard-656A3878: G***; kibuzzard-656A3878
kibuzzard-656A4896: G***; kibuzzard-656A4896
kibuzzard-6569BE4A: G***; kibuzzard-6569BE4A
kibuzzard-6569BE28: G***; kibuzzard-6569BE28
kibuzzard-6569BE57: G***; kibuzzard-6569BE57
kibuzzard-6569BF02: G***; kibuzzard-6569BF02
kibuzzard-6569F7FC: G***; kibuzzard-6569F7FC
kibuzzard-6569F8A4: G***; kibuzzard-6569F8A4

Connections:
3.3V: C1.2, C7.1, C11.1, C13.1, JP1.2 (B), JP2.2 (B), R8.1, U3.3 (3V3), U6.5 (VOUT), U10.27 (3.3V)
3.3V_P: C3.1, C4.1, C5.1, C8.1, D6.4 (VDD), J2.4 (VDD), J4.2, R1.1, R2.1, R3.1, R4.1, R5.1, R6.1, R12.1, R15.1, U1.5 (VOUT)
EN: R13.2, U6.3 (EN), U10.11 (EN)
ESP0/STAT: R7.1, SW1.1, TP2.1, U3.4 (IO0)
ESP1: U3.5 (IOA1), U10.3 (GPIO6)
ESP2: U3.6 (IOA2), U10.4 (GPIO5)
ESP4: U3.8 (IOA4), U10.5 (GPIO4)
ESP5: U3.9 (IOA5), U10.6 (GPIO3)
ESP6: U3.10 (IOA6), U10.7 (GPIO2)
ESP7: U3.11 (IOA7), U10.8 (GPIO1)
ESP8/SDA: J4.3, R15.2, U3.12 (IOA8), U4.8 (SDA), U10.1 (SDA)
ESP9/SCL: J4.4, R12.2, U3.13 (IOA9), U4.7 (SCL), U10.2 (SCL)
ESP10/A0: U3.14 (IOA10), U10.24 (A0)
ESP11/PICO: U3.15 (IOA11), U10.17 (PICO)
ESP12/SCK: U3.16 (IOA12), U10.18 (SCK)
ESP13/POCI: U3.17 (IOA13), U10.16 (POCI)
ESP14/A1: U3.18 (IOA14), U10.23 (A1)
ESP15/A2: U3.19 (IOA15), U10.22 (A2)
ESP16/A3: U3.20 (IOA16), U10.21 (A3)
ESP17/A4: U3.21 (IOA17), U10.20 (A4)
ESP18/A5: U3.22 (IOA18), U10.19 (A5)
ESP19/D-: J1.A7 (D-), J1.B7 (D-), U2.4 (I/O3), U3.23 (IOA19)
ESP20/D+: J1.A6 (D+), J1.B6 (D+), U2.6 (I/O4), U3.24 (IOA20)
ESP21: U3.25 (IO21), U10.9 (GPIO0)
ESP33/SDIO3: J2.2 (DAT3/~CS), R6.2, U3.28 (IO33)
ESP34/SDIO_CMD: J2.3 (CMD/SDI), R1.2, U3.29 (IO34)
ESP35/~ALRT: U3.31 (IO35), U4.5 (~ALRT)
ESP38/SDIO_CLK: J2.5 (CLK/SCK), R2.2, U3.34 (IO38)
ESP39/SDIO0: J2.7 (DAT0/SDO), R3.2, U3.35 (IO39)
ESP40/SDIO1: J2.8 (DAT1), R4.2, U3.36 (IO40)
ESP42/FREE: U3.38 (IO42), U10.13 (FREEBIE)
ESP43/TXO: U3.39 (TXD0/IO43), U10.14 (TX)
ESP44/RXI: U3.40 (RXD0/IO44), U10.15 (RX)
ESP45/Q_EN: R17.2, R19.1, U1.3 (EN), U3.41 (IO45)
ESP46/LED: D6.3 (DIN), U3.44 (IO46)
ESP47/SDIO2: J2.1 (DAT2), R5.2, U3.27 (IO47)
ESP48/SDIO_~DET: J2.9 (DET), U3.30 (IO48)
ESP~RST: C6.1, R8.2, SW2.1, U3.45 (EN), U10.28 (~RESET)
GND: C1.1, C2.2, C3.2, C4.2, C5.2, C6.2, C7.2, C8.2, C9.2, C10.2, C11.2, C12.2, C13.2, C14.2, D1.1 (K), D5.1 (K), D6.2 (VSS), J1.GND, J1.S (SHIELD), J2.6 (VSS), J2.10 (SHIELD), J3.1 (-), J4.1, R10.1, R11.2, R16.2, R19.2, SW1.2, SW2.2, U1.2 (GND), U2.2 (GND), U3.1 (GND), U3.2 (GND), U3.42 (GND), U3.43 (GND), U3.46 (GND), U3.47 (GND), U3.48 (GND), U3.49 (GND), U3.50 (GND), U3.51 (GND), U3.52 (GND), U3.53 (GND), U3.54 (GND), U3.55 (GND), U3.56 (GND), U3.57 (GND), U3.58 (GND), U3.59 (GND), U3.60 (GND), U3.61 (GND), U3.62 (GND), U3.63 (GND), U3.64 (GND), U3.65 (GND), U4.1 (CTG), U4.4 (GND), U4.6 (QSTRT), U4.9 (GND), U5.2 (GND), U6.2 (GND), U10.25 (GND)
unnamed: D1.2 (A), R7.2
unnamed: D4.2 (A), R14.1
unnamed: D4.1 (K), U5.1 (STAT)
unnamed: D5.2 (A), R9.2
unnamed: D6.1 (DOUT), TP1.1
unnamed: J1.A5 (CC1), R11.1
unnamed: J1.B5 (CC2), R10.2
unnamed: JP1.1 (A), R9.1
unnamed: JP2.1 (A), R17.1
unnamed: JP3.1 (A), R14.2
unnamed: R16.1, U5.5 (PROG)
VBATT: C2.1, C12.1, D3.A, J3.2 (+), U4.2 (CELL), U4.3 (VDD), U5.3 (V_{BAT}), U10.12 (V_BATT)
VIN: C10.1, C14.1, D2.C, D3.C, R13.1, U1.1 (VIN), U6.1 (VIN)
VUSB: C9.1, D2.A, J1.VBUS, JP3.2 (B), U2.5 (VCC), U5.4 (VIN), U10.10 (V_USB)

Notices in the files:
parts and their libraries:
https://creativecommons.org/licenses/by-sa/4.0
Released under the Creative Commons Attribution Share-Alike 4.0 License
